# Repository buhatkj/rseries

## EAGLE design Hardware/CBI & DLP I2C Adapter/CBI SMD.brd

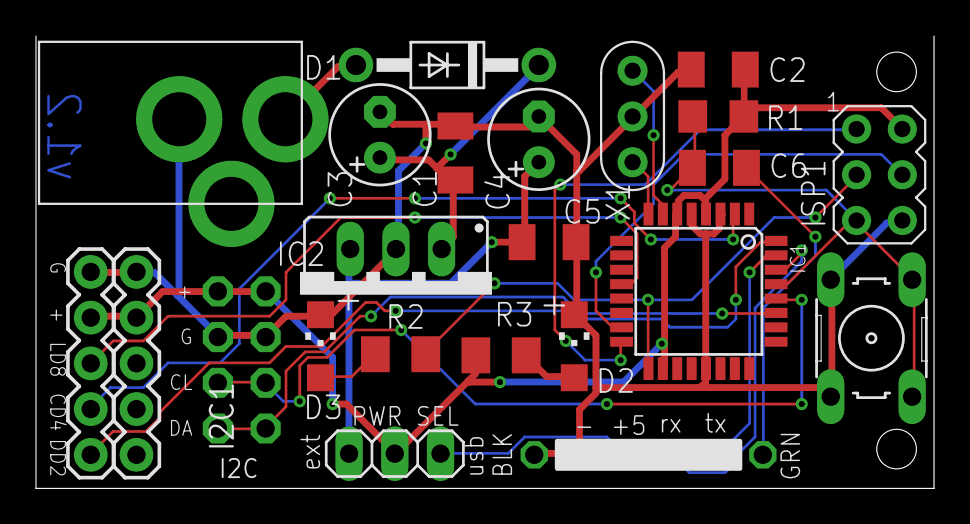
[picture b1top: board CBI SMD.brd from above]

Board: 2 copper layers, 49.9 x 25.1 mm, 25 parts (1 on the bottom side), 22 nets.

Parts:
C1, C2, C5, C6: 0.1uF; C1206K
C3: 10uF/25V; E2,5-6
C4: 100/6VuF; E2,5-6
D1: 1N4001; DO41-10
D2: CHIPLED_1206
D3: Green; CHIPLED_1206
I2C, I2C1: 1X04-CB
IC1: MEGA48/88/168-AU; TQFP32-08
IC2: 78XXS
ISP1: AVRISP-6; AVRISP
J1: 2.1MMJACK; PJ-102A
JP7: 1X06-CLEAN
PWR_SEL: 1X03
R1: 10K; R1206
R2, R3: 1.0 K; M1206
S1: RESET; B3F-10XX
TEECES, TEECES1: 1X05
U$2: RSERIES-OSHW-LOGOMEDIUM; RSERIES-OSHW-LOGO-MEDIUM
X1: 16.00MHz; CERM_OSC

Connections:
+5V: C2.1, I2C.4, I2C1.4, IC1.4, IC1.6, IC1.18, ISP1.2, PWR_SEL.2, R1.1, R2.1, TEECES.4, TEECES1.4
+9V: C1.1, C3.+, D1.C, IC2.IN
ANALOG4: I2C.1, I2C1.1, IC1.27
ANALOG5: I2C.2, I2C1.2, IC1.28
DIGITAL2: IC1.32, TEECES.1
DIGITAL4: IC1.2, TEECES.2
DIGITAL8: IC1.12, TEECES.3
GND: C1.2, C2.2, C3.-, C4.-, C5.2, D2.C, D3.C, I2C.3, I2C1.3, IC1.3, IC1.5, IC1.21, IC2.GND, ISP1.6, J1.RING, JP7.1, JP7.2, S1.1, S1.2, TEECES.5, TEECES1.5, X1.P$2
MISO: IC1.16, ISP1.1
MOSI: IC1.15, ISP1.4
unnamed: IC1.7, X1.P$1
unnamed: IC1.8, X1.P$3
unnamed: D2.A, R2.2
unnamed: D3.A, R3.2
unnamed: D1.A, J1.TIP
unnamed: C4.+, C5.1, IC2.OUT, PWR_SEL.1
RST: C6.2, IC1.29, ISP1.5, R1.2, S1.3, S1.4
RTS#: C6.1, JP7.6
RXD: IC1.30, JP7.4
SCK: IC1.17, ISP1.3, R3.1
TXD: IC1.31, JP7.5
USB_5V: JP7.3, PWR_SEL.3

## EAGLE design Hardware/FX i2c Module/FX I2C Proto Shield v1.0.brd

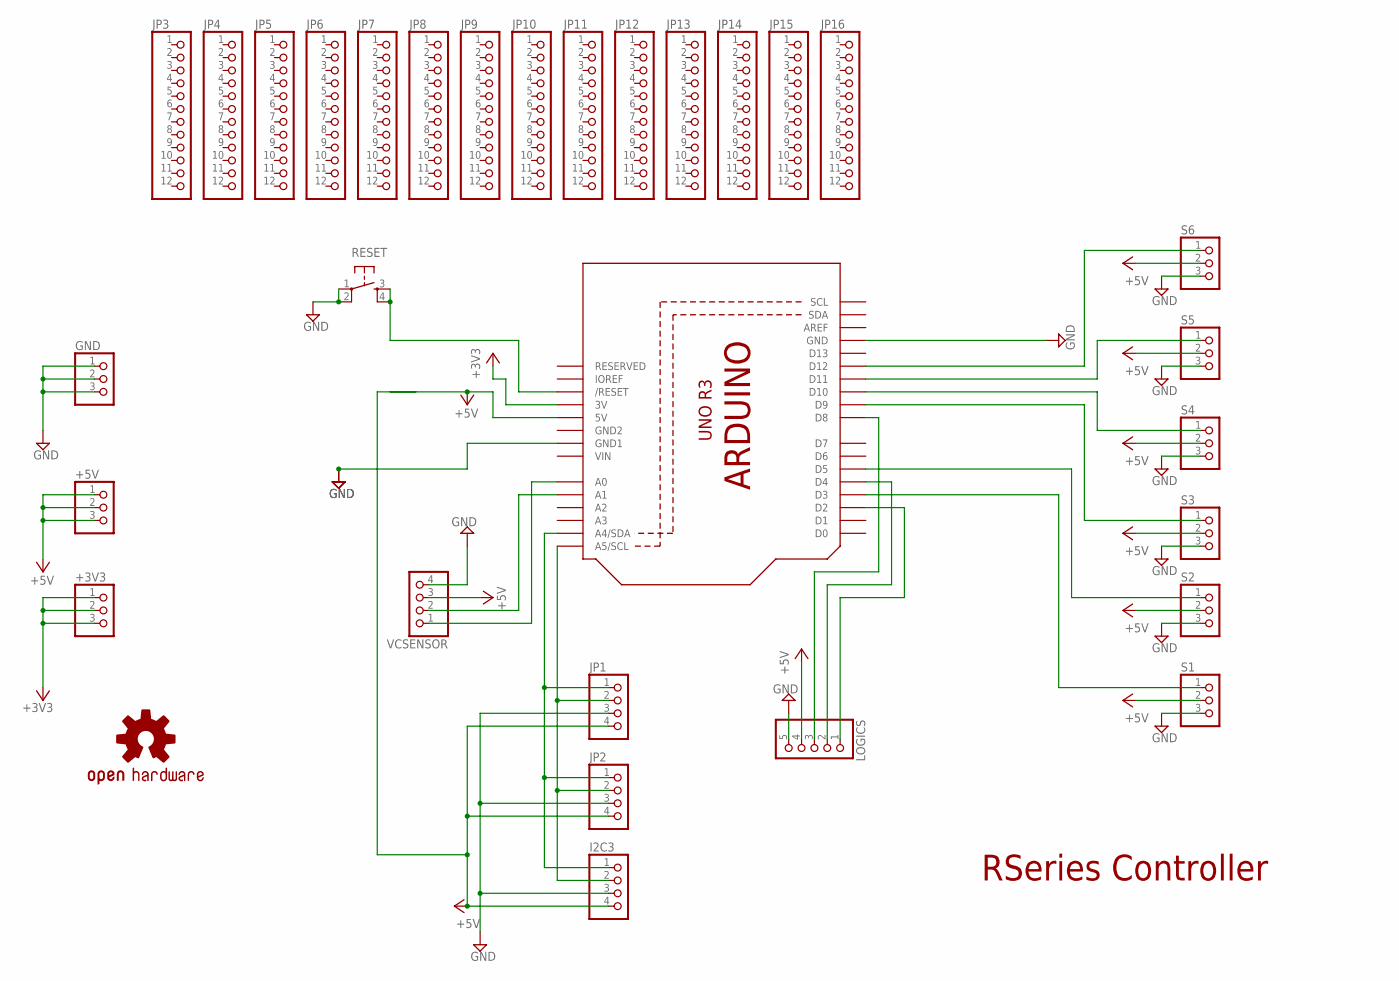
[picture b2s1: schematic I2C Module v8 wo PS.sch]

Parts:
+3V3, +5V: PINHD-1X3CB; 1X03-CLEANBIG
GND: PINHD-1X3CB; 1X03-CLEANBIG
I2C3: PINHD-1X4; 1X04
JP1, JP2: PINHD-1X4; 1X04
JP3, JP4, JP5, JP6, JP7, JP8, JP9, JP10, JP11, JP12, JP13, JP14, JP15, JP16: PINHD-1X12-CB; 1X12-CB
LOGICS: PINHD-1X5; 1X05
RESET: TAC_SWITCHPTH; TACTILE-PTH
S1, S2, S3, S4, S5, S6: PINHD-1X3; 1X03
U1: ARDUINOR3-DIMENSION; ARDUINOR3
U$1: OSHW-LOGOM; OSHW-LOGO-M
VCSENSOR: PINHD-1X4; 1X04

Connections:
+3V3: +3V3.1, +3V3.2, +3V3.3, U1.3V
+5V: +5V.1, +5V.2, +5V.3, I2C3.4, JP1.4, JP2.4, LOGICS.4, S1.2, S2.2, S3.2, S4.2, S5.2, S6.2, U1.5V, VCSENSOR.3
GND: GND.1, GND.2, GND.3, I2C3.3, JP1.3, JP2.3, LOGICS.5, RESET.1, RESET.2, S1.3, S2.3, S3.3, S4.3, S5.3, S6.3, U1.GND, U1.GND1, VCSENSOR.4
GND2: U1.GND2
unnamed 4: U1.A0, VCSENSOR.1; also elsewhere on the board
unnamed 5: LOGICS.3, U1.D8; also elsewhere on the board
unnamed 6: U1.A1, VCSENSOR.2; also elsewhere on the board
unnamed 7: S1.1, U1.D3; also elsewhere on the board
unnamed 8: S2.1, U1.D5; also elsewhere on the board
unnamed 9: S3.1, U1.D9; also elsewhere on the board
unnamed 10: S4.1, U1.D10; also elsewhere on the board
unnamed 11: S5.1, U1.D11; also elsewhere on the board
unnamed 12: S6.1, U1.D12; also elsewhere on the board
unnamed 13: LOGICS.2, U1.D4; also elsewhere on the board
unnamed 14: LOGICS.1, U1.D2; also elsewhere on the board
unnamed: RESET.3, RESET.4, U1.RESET (/RESET)
unnamed 17: U1.A2; also elsewhere on the board
unnamed 18: I2C3.2, JP1.2, JP2.2, U1.A5 (A5/SCL); also elsewhere on the board
unnamed 19: I2C3.1, JP1.1, JP2.1, U1.A4 (A4/SDA); also elsewhere on the board
unnamed 20: U1.A3; also elsewhere on the board
unnamed 21: U1.D0; also elsewhere on the board
unnamed 22: U1.D1; also elsewhere on the board
unnamed 23: U1.D6; also elsewhere on the board
unnamed 24: U1.D7; also elsewhere on the board
unnamed 25: U1.D13; also elsewhere on the board
VIN: U1.VIN

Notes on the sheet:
RSeries Controller

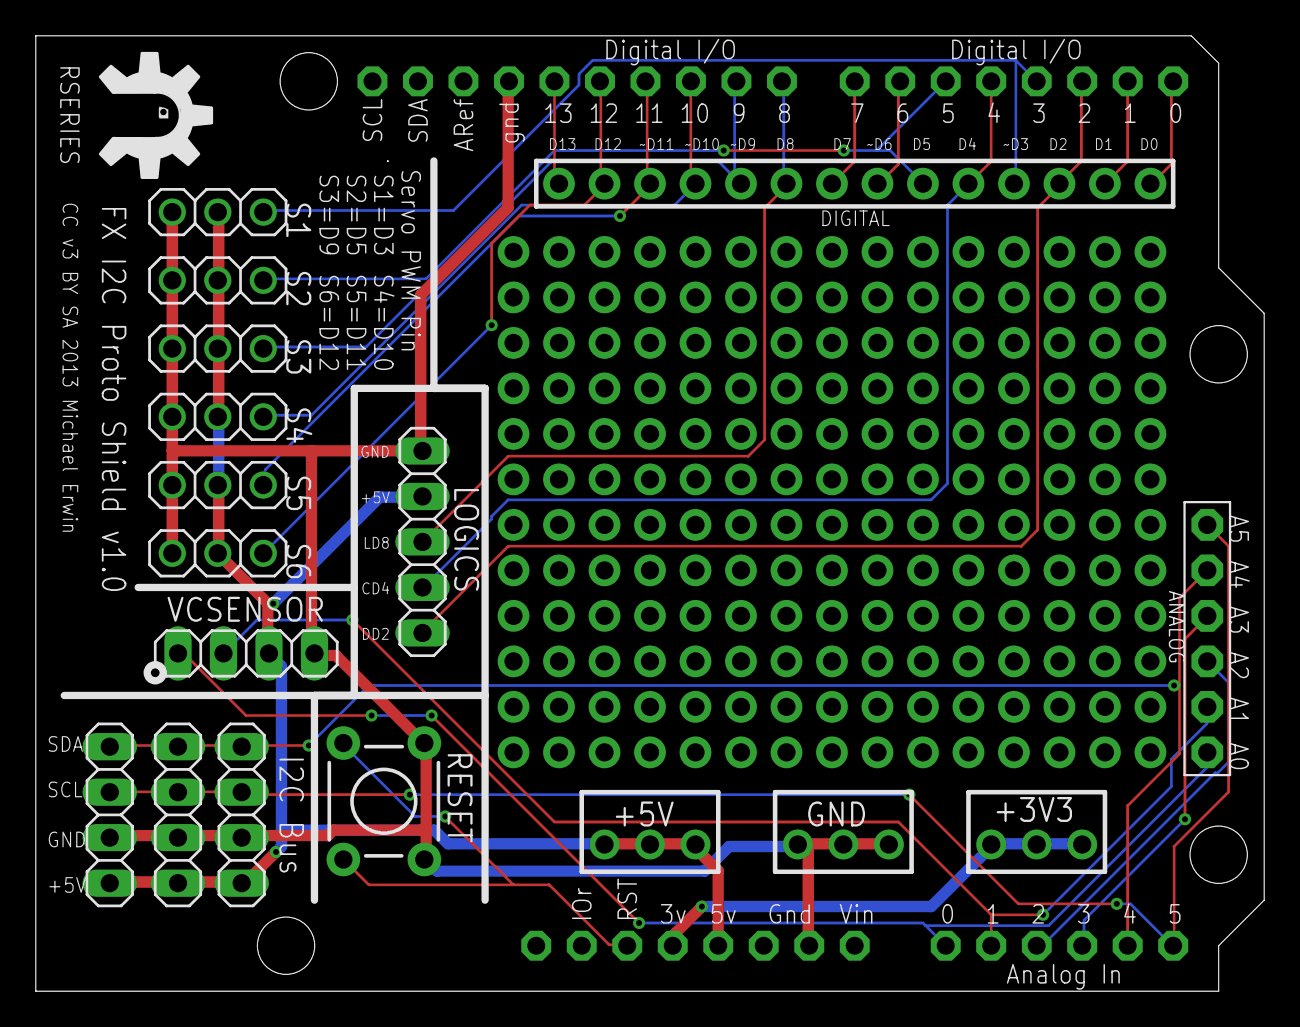
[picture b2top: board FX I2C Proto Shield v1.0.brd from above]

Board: 2 copper layers, 68.6 x 53.3 mm, 34 parts (0 on the bottom side), 24 nets.

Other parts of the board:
ANALOG: 1X06-BIG
DIGITAL: 1X14-CB
JP17: 1X12-CB

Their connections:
unnamed 4: ANALOG.1; also elsewhere on the board
unnamed 5: DIGITAL.9; also elsewhere on the board
unnamed 6: ANALOG.2; also elsewhere on the board
unnamed 7: DIGITAL.4; also elsewhere on the board
unnamed 8: DIGITAL.6; also elsewhere on the board
unnamed 9: DIGITAL.10; also elsewhere on the board
unnamed 10: DIGITAL.11; also elsewhere on the board
unnamed 11: DIGITAL.12; also elsewhere on the board
unnamed 12: DIGITAL.13; also elsewhere on the board
unnamed 13: DIGITAL.5; also elsewhere on the board
unnamed 14: DIGITAL.3; also elsewhere on the board
unnamed 17: ANALOG.3; also elsewhere on the board
unnamed 18: ANALOG.6; also elsewhere on the board
unnamed 19: ANALOG.5; also elsewhere on the board
unnamed 20: ANALOG.4; also elsewhere on the board
unnamed 21: DIGITAL.1; also elsewhere on the board
unnamed 22: DIGITAL.2; also elsewhere on the board
unnamed 23: DIGITAL.7; also elsewhere on the board
unnamed 24: DIGITAL.8; also elsewhere on the board
unnamed 25: DIGITAL.14; also elsewhere on the board

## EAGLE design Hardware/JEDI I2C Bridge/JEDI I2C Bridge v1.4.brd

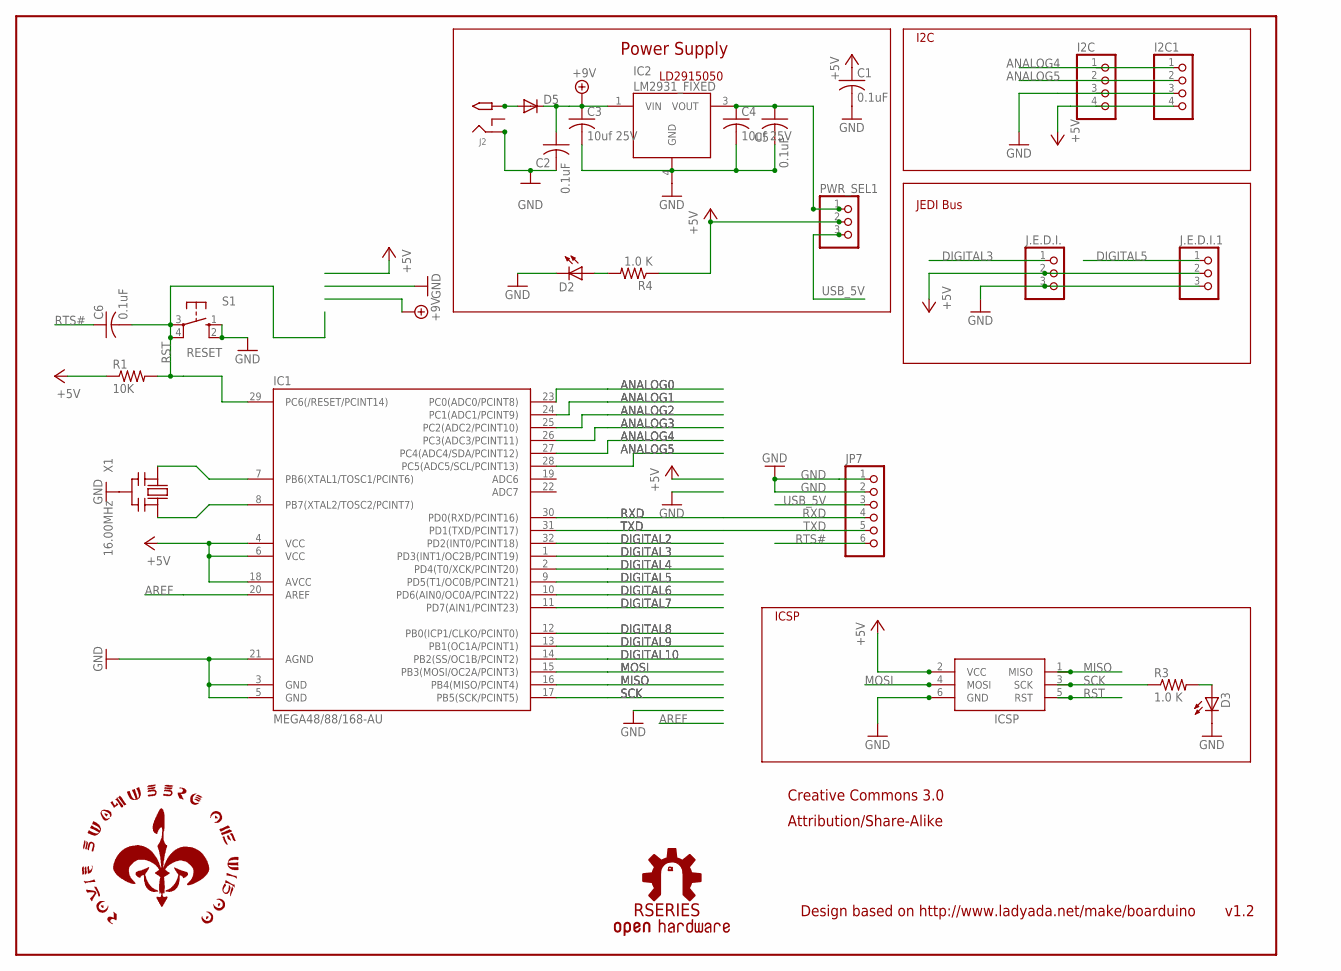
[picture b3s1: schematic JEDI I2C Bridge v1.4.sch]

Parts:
C1, C2, C5, C6: 0.1uF; C1206K
C3, C4: 10uf 25V; C1206K
D2: LEDCHIPLED_1206; CHIPLED_1206
D3: Green; CHIPLED_1206
D5: DIODE-SMB; SMB
I2C, I2C1: PINHD-1X4CB; 1X04-CB
IC1: MEGA48/88/168-AU; TQFP32-08
IC2: LM2931_FIXED; DPAK
ICSP: AVRISP-6; AVRISP
J2: 2.1MMJACK; PJ-102A
J.E.D.I., J.E.D.I.1: PINHD-1X3; 1X03
JP7: PINHD-1X6CLEAN; 1X06-CLEAN
PWR_SEL1: PINHD-1X3; 1X03
R1: 10K; R1206
R3, R4: 1.0 K; M1206
S1: RESET; B3F-10XX
U$2: RSERIES-OSHW-LOGOMEDIUM; RSERIES-OSHW-LOGO-MEDIUM
U$3: ROYAL-ENGINEERS-OF-NABOOSMALL; ROYAL-ENGINEERS-OF-NABOO-SMALL
X1: 16.00MHz; CERM_OSC

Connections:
+5V: C1.1, I2C.4, I2C1.4, IC1.4 (VCC), IC1.6 (VCC), IC1.18 (AVCC), ICSP.2 (VCC), J.E.D.I..2, J.E.D.I.1.2, PWR_SEL1.2, R1.1, R4.1
+9V: C2.1, C3.1, D5.C, IC2.1 (VIN)
ANALOG0: IC1.23 (PC0(ADC0/PCINT8))
ANALOG1: IC1.24 (PC1(ADC1/PCINT9))
ANALOG2: IC1.25 (PC2(ADC2/PCINT10))
ANALOG3: IC1.26 (PC3(ADC3/PCINT11))
ANALOG4: I2C.1, I2C1.1, IC1.27 (PC4(ADC4/SDA/PCINT12))
ANALOG5: I2C.2, I2C1.2, IC1.28 (PC5(ADC5/SCL/PCINT13))
AREF: IC1.20 (AREF)
DIGITAL2: IC1.32 (PD2(INT0/PCINT18))
DIGITAL3: IC1.1 (PD3(INT1/OC2B/PCINT19)), J.E.D.I..1
DIGITAL4: IC1.2 (PD4(T0/XCK/PCINT20))
DIGITAL5: IC1.9 (PD5(T1/OC0B/PCINT21)), J.E.D.I.1.1
DIGITAL6: IC1.10 (PD6(AIN0/OC0A/PCINT22))
DIGITAL7: IC1.11 (PD7(AIN1/PCINT23))
DIGITAL8: IC1.12 (PB0(ICP1/CLKO/PCINT0))
DIGITAL9: IC1.13 (PB1(OC1A/PCINT1))
DIGITAL10: IC1.14 (PB2(SS/OC1B/PCINT2))
GND: C1.2, C2.2, D2.C, D3.C, I2C.3, I2C1.3, IC1.3 (GND), IC1.5 (GND), IC1.21 (AGND), IC2.4 (GND), ICSP.6 (GND), J2.RING, J.E.D.I..3, J.E.D.I.1.3, JP7.1, JP7.2, S1.1 (S), S1.2 (S1), X1.P$2 (GND)
MISO: IC1.16 (PB4(MISO/PCINT4)), ICSP.1 (MISO)
MOSI: IC1.15 (PB3(MOSI/OC2A/PCINT3)), ICSP.4 (MOSI)
unnamed: IC1.7 (PB6(XTAL1/TOSC1/PCINT6)), X1.P$1 (IN)
unnamed: IC1.8 (PB7(XTAL2/TOSC2/PCINT7)), X1.P$3 (OUT)
unnamed: D3.A, R3.2
unnamed: D2.A, R4.2
unnamed: D5.A, J2.TIP
unnamed: C3.2, C4.2, C5.2
unnamed: C4.1, C5.1, IC2.3 (VOUT), PWR_SEL1.1
RST: C6.2, IC1.29 (PC6(/RESET/PCINT14)), ICSP.5 (RST), R1.2, S1.3, S1.4 (P1)
RTS#: C6.1, JP7.6
RXD: IC1.30 (PD0(RXD/PCINT16)), JP7.4
SCK: IC1.17 (PB5(SCK/PCINT5)), ICSP.3 (SCK), R3.1
TXD: IC1.31 (PD1(TXD/PCINT17)), JP7.5
USB_5V: JP7.3, PWR_SEL1.3

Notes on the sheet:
v1.2
Design based on http://www.ladyada.net/make/boarduino
Creative Commons 3.0
Attribution/Share-Alike
JEDI Bus
I2C
ICSP
Power Supply
LD2915050

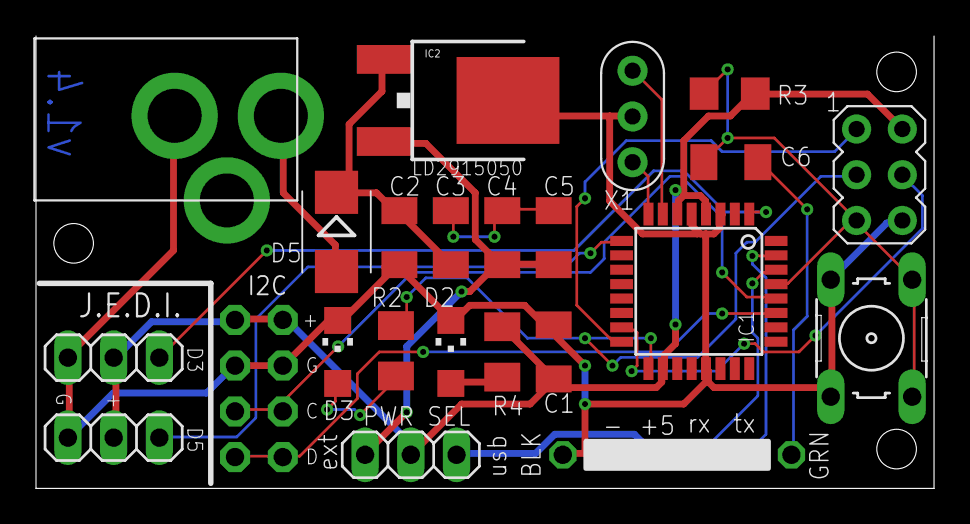
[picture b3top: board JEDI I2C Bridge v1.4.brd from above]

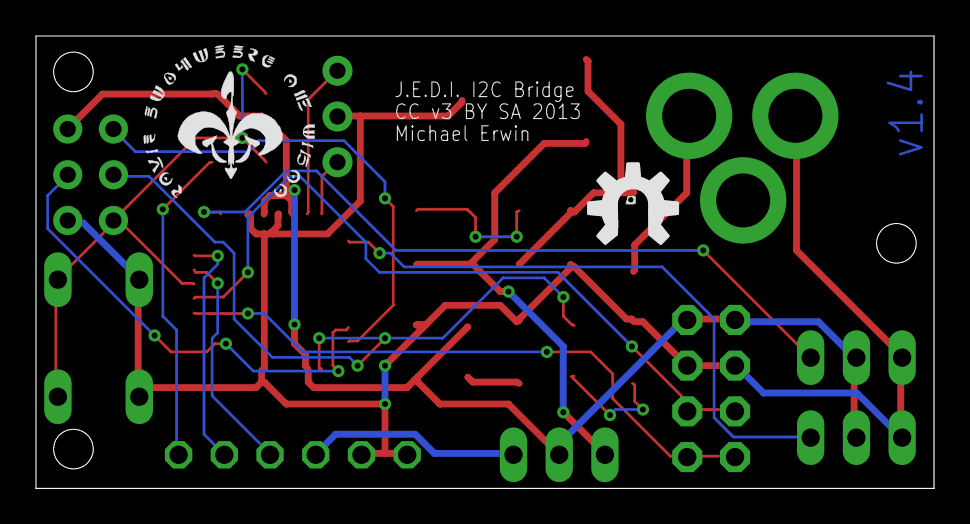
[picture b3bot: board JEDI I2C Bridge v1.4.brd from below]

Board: 2 copper layers, 49.9 x 25.1 mm, 26 parts (2 on the bottom side), 22 nets.

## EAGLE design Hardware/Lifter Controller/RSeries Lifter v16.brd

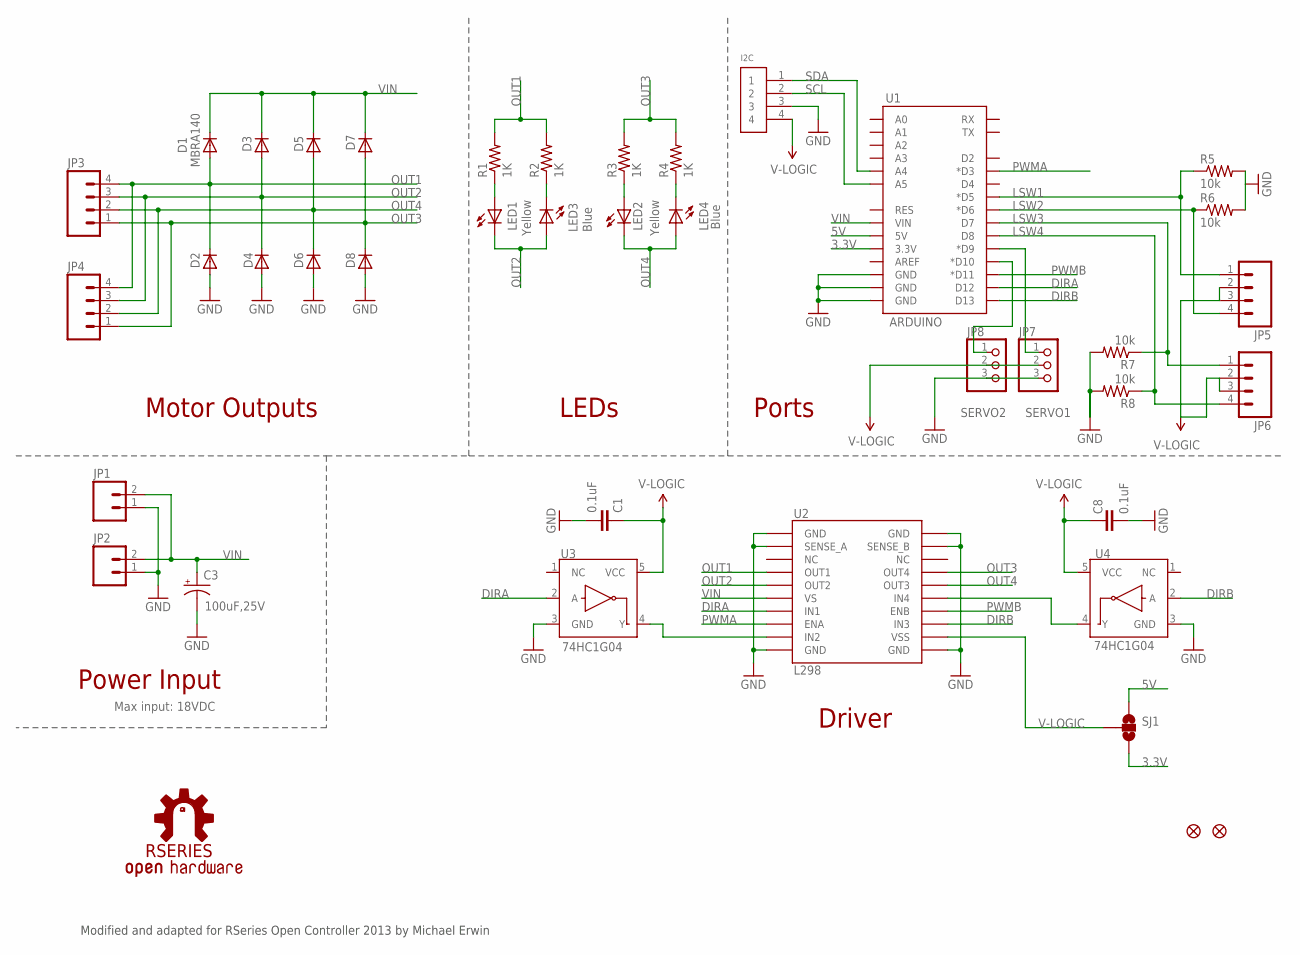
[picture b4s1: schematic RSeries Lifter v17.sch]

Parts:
C1, C8: 0.1uF; 0402-CAP
C3: 100uF,25V; NIPPON_F80
D1, D2, D3, D4, D5, D6, D7, D8: MBRA140; SMA-DIODE
I2C: 1X4-CLEANBIG; 1X04-CLEANBIG
JP1: M02PTH; 1X02
JP2: M023.5MM; SCREWTERMINAL-3.5MM-2
JP3, JP5, JP6: M04SCREW; SCREWTERMINAL-3.5MM-4
JP4: M04PTH; 1X04
JP7, JP8: PINHD-1X3CB; 1X03-CLEANBIG
LED1, LED2: Yellow; LED-1206
LED3, LED4: Blue; LED-1206
R1, R2, R3, R4: 1K; 0805
R5, R6, R7, R8: 10k; 0805
SJ1: SOLDERJUMPER_2WAYPASTE1&2; SJ_3_PASTE1&2
U1: ARDUINO; DUEMILANOVE_SHIELD_NOLABELS
U2: L298; POWERSO20
U3, U4: 74HC1G04; SOT23-5
U$3, U$4: FIDUCIAL1X2; FIDUCIAL-1X2
U$7: RSERIES-OSHW-LOGOMEDIUM; RSERIES-OSHW-LOGO-MEDIUM

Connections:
3.3V: SJ1.3, U1.3.3V
5V: I2C.4, JP5.2, JP5.3, JP6.2, JP6.3, JP7.2, JP8.2, SJ1.1, U1.5V
DIRA: U1.D12, U2.P$7 (IN1), U3.2 (A)
DIRB: U1.D13, U2.P$13 (IN3), U4.2 (A)
GND: C1.2, C3.-, C8.2, D2.A, D4.A, D6.A, D8.A, I2C.3, JP1.1, JP2.1, JP7.3, JP8.3, R5.2, R6.2, R7.2, R8.2, U1.GND@0 (GND), U1.GND@1 (GND), U1.GND@2 (GND), U2.P$1 (GND), U2.P$2 (SENSE_A), U2.P$10 (GND), U2.P$11 (GND), U2.P$19 (SENSE_B), U2.P$20 (GND), U3.3 (GND), U4.3 (GND)
unnamed: U2.P$9 (IN2), U3.4 (Y)
unnamed: U2.P$15 (IN4), U4.4 (Y)
unnamed: JP5.1, R5.1, U1.D5 (*D5)
unnamed: LED1.A, R1.1
unnamed: LED3.C, R2.1
unnamed: JP6.1, R7.1, U1.D7
unnamed: JP6.4, R8.1, U1.D8
unnamed: LED2.A, R3.1
unnamed: LED4.C, R4.1
unnamed: JP7.1, U1.D9 (*D9)
unnamed: JP8.1, U1.D10 (*D10)
unnamed: JP5.4, R6.1, U1.D6 (*D6)
unnamed: I2C.1, U1.A4
unnamed: I2C.2, U1.A5
OUT1: D1.A, D2.C, JP3.4, JP4.4, R1.2, R2.2, U2.P$4 (OUT1)
OUT2: D3.A, D4.C, JP3.3, JP4.3, LED1.C, LED3.A, U2.P$5 (OUT2)
OUT3: D7.A, D8.C, JP3.1, JP4.1, R3.2, R4.2, U2.P$17 (OUT4)
OUT4: D5.A, D6.C, JP3.2, JP4.2, LED2.C, LED4.A, U2.P$16 (OUT3)
PWMA: U1.D3 (*D3), U2.P$8 (ENA)
PWMB: U1.D11 (*D11), U2.P$14 (ENB)
V-LOGIC: C1.1, C8.1, SJ1.2, U2.P$12 (VSS), U3.5 (VCC), U4.5 (VCC)
VIN: C3.+, D1.C, D3.C, D5.C, D7.C, JP1.2, JP2.2, U1.VIN, U2.P$6 (VS)

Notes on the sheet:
Motor Outputs
LEDs
Ports
Driver
Power Input
Max input: 18VDC
Modified and adapted for RSeries Open Controller 2013 by Michael Erwin
SERVO1
SERVO2
SDA
SCL
LSW1
LSW2
LSW3
LSW4

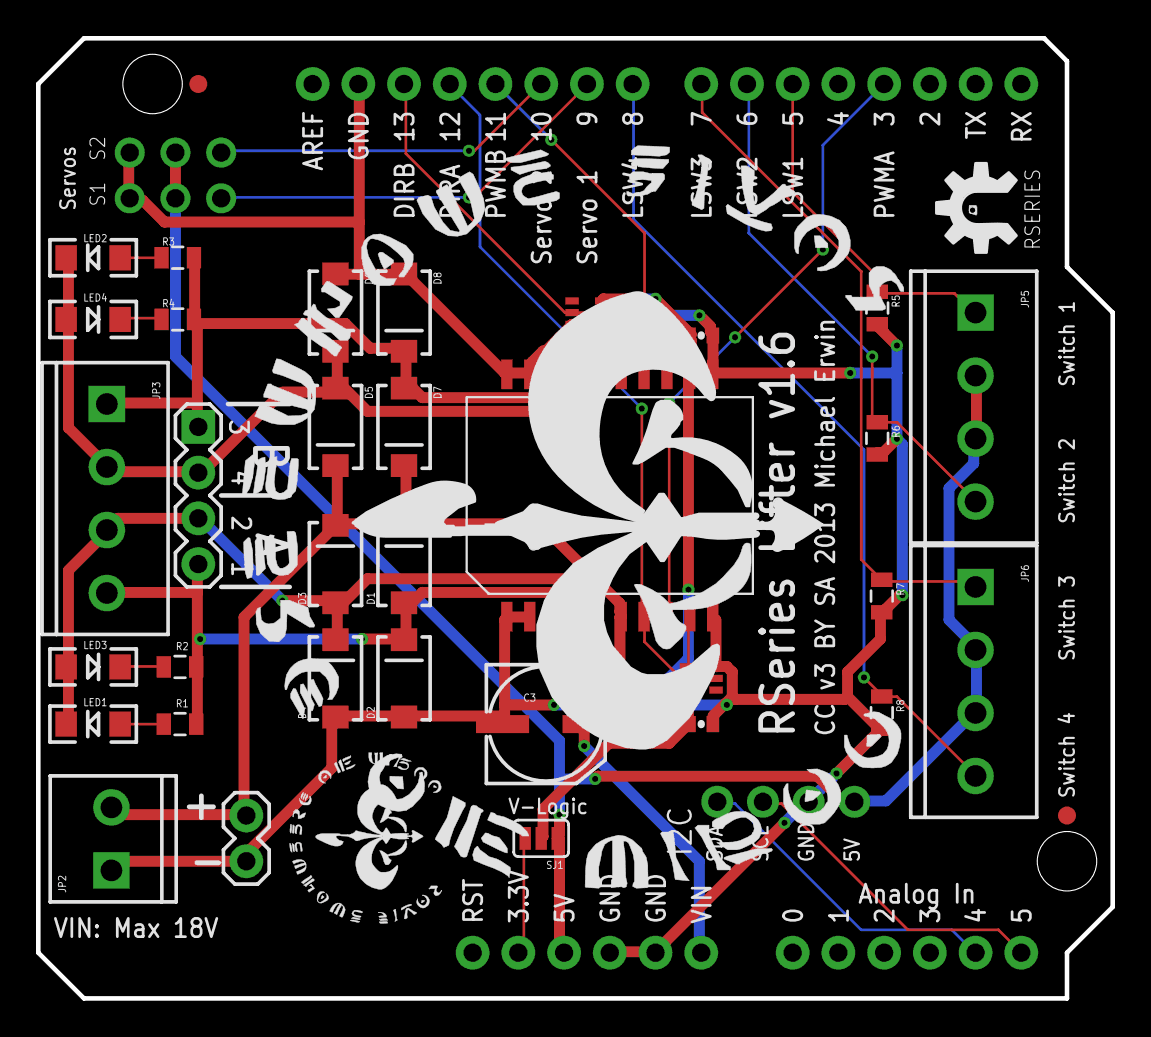
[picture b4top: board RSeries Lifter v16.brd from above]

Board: 2 copper layers, 59.7 x 53.3 mm, 42 parts (1 on the bottom side), 27 nets.

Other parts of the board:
U$6: ROYAL-ENGINEERS-OF-NABOO-SMALL
U$10: ROYAL-ENGINEERS-OF-NABOO-BOTTOM-LARGE

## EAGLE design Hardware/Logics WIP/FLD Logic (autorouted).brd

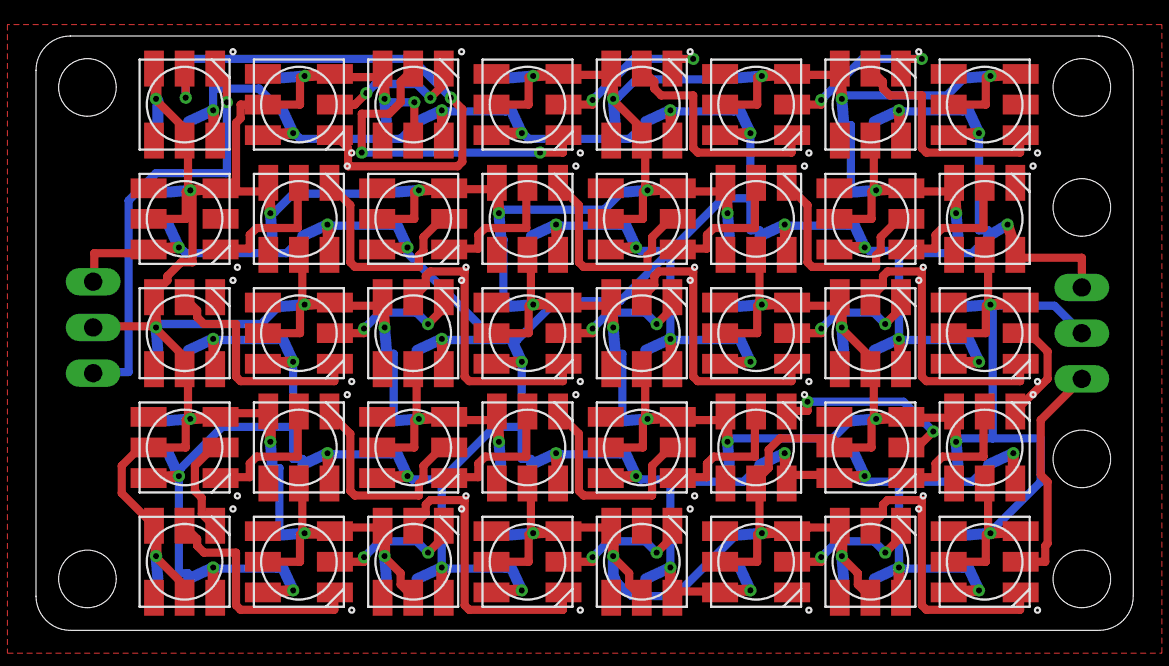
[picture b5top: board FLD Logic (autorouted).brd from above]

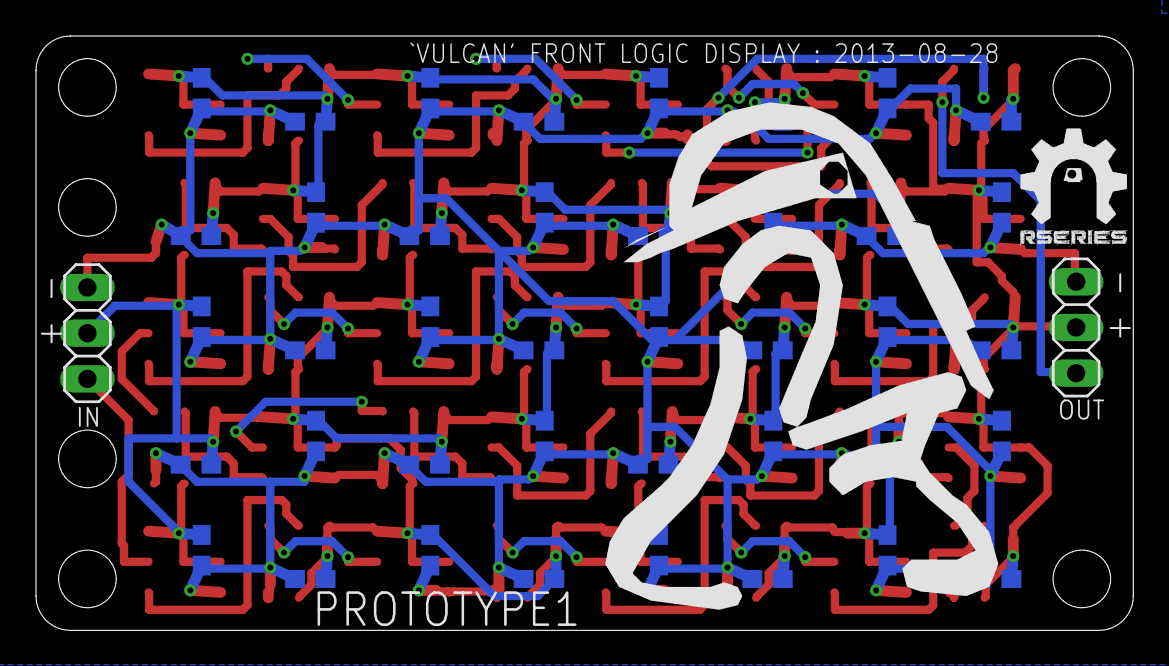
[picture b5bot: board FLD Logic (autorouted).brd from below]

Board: 2 copper layers, 61.0 x 33.0 mm, 83 parts (43 on the bottom side), 40 nets.

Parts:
C1, C2, C3, C4, C5, C6, C7, C8, C9, C10, C11, C12, C13, C14, C15, C16, C17, C18, C19, C20, C21, C22, C23, C24, C25, C26, C27, C28, C29, C30, C31, C32, C33, C34, C35, C36, C37, C38, C39, C40: 0.1uF; C0603
IN: 1X03
LED1, LED2, LED3, LED4, LED5, LED6, LED7, LED8, LED9, LED10, LED11, LED12, LED13, LED14, LED15, LED16, LED17, LED18, LED19, LED20, LED21, LED22, LED23, LED24, LED25, LED26, LED27, LED28, LED29, LED30, LED31, LED32, LED33, LED34, LED35, LED36, LED37, LED38, LED39, LED40: WS2812
OUT: 1X03
U$1: RSERIES-OSHW-LOGO-SMALL

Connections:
+5V: C1.1, C2.1, C3.1, C4.1, C5.1, C6.1, C7.1, C8.1, C9.1, C10.1, C11.1, C12.1, C13.1, C14.1, C15.1, C16.1, C17.1, C18.1, C19.1, C20.1, C21.1, C22.1, C23.1, C24.1, C25.1, C26.1, C27.1, C28.1, C29.1, C30.1, C31.1, C32.1, C33.1, C34.1, C35.1, C36.1, C37.1, C38.1, C39.1, C40.1, IN.2, LED1.LEDVDD, LED1.VDD, LED2.LEDVDD, LED2.VDD, LED3.LEDVDD, LED3.VDD, LED4.LEDVDD, LED4.VDD, LED5.LEDVDD, LED5.VDD, LED6.LEDVDD, LED6.VDD, LED7.LEDVDD, LED7.VDD, LED8.LEDVDD, LED8.VDD, LED9.LEDVDD, LED9.VDD, LED10.LEDVDD, LED10.VDD, LED11.LEDVDD, LED11.VDD, LED12.LEDVDD, LED12.VDD, LED13.LEDVDD, LED13.VDD, LED14.LEDVDD, LED14.VDD, LED15.LEDVDD, LED15.VDD, LED16.LEDVDD, LED16.VDD, LED17.LEDVDD, LED17.VDD, LED18.LEDVDD, LED18.VDD, LED19.LEDVDD, LED19.VDD, LED20.LEDVDD, LED20.VDD, LED21.LEDVDD, LED21.VDD, LED22.LEDVDD, LED22.VDD, LED23.LEDVDD, LED23.VDD, LED24.LEDVDD, LED24.VDD, LED25.LEDVDD, LED25.VDD, LED26.LEDVDD, LED26.VDD, LED27.LEDVDD, LED27.VDD, LED28.LEDVDD, LED28.VDD, LED29.LEDVDD, LED29.VDD, LED30.LEDVDD, LED30.VDD, LED31.LEDVDD, LED31.VDD, LED32.LEDVDD, LED32.VDD, LED33.LEDVDD, LED33.VDD, LED34.LEDVDD, LED34.VDD, LED35.LEDVDD, LED35.VDD, LED36.LEDVDD, LED36.VDD, LED37.LEDVDD, LED37.VDD, LED38.LEDVDD, LED38.VDD, LED39.LEDVDD, LED39.VDD, LED40.LEDVDD, LED40.VDD, OUT.2
DIN: IN.3, LED1.DI
DOUT: LED40.DO, OUT.3
GND: C1.2, C2.2, C3.2, C4.2, C5.2, C6.2, C7.2, C8.2, C9.2, C10.2, C11.2, C12.2, C13.2, C14.2, C15.2, C16.2, C17.2, C18.2, C19.2, C20.2, C21.2, C22.2, C23.2, C24.2, C25.2, C26.2, C27.2, C28.2, C29.2, C30.2, C31.2, C32.2, C33.2, C34.2, C35.2, C36.2, C37.2, C38.2, C39.2, C40.2, IN.1, LED1.VSS, LED2.VSS, LED3.VSS, LED4.VSS, LED5.VSS, LED6.VSS, LED7.VSS, LED8.VSS, LED9.VSS, LED10.VSS, LED11.VSS, LED12.VSS, LED13.VSS, LED14.VSS, LED15.VSS, LED16.VSS, LED17.VSS, LED18.VSS, LED19.VSS, LED20.VSS, LED21.VSS, LED22.VSS, LED23.VSS, LED24.VSS, LED25.VSS, LED26.VSS, LED27.VSS, LED28.VSS, LED29.VSS, LED30.VSS, LED31.VSS, LED32.VSS, LED33.VSS, LED34.VSS, LED35.VSS, LED36.VSS, LED37.VSS, LED38.VSS, LED39.VSS, LED40.VSS, OUT.1
unnamed: LED4.DO, LED5.DI
unnamed: LED5.DO, LED6.DI
unnamed: LED7.DO, LED8.DI
unnamed: LED6.DO, LED7.DI
unnamed: LED17.DO, LED18.DI
unnamed: LED9.DO, LED10.DI
unnamed: LED10.DO, LED11.DI
unnamed: LED12.DO, LED13.DI
unnamed: LED13.DO, LED14.DI
unnamed: LED1.DO, LED2.DI
unnamed: LED2.DO, LED3.DI
unnamed: LED11.DO, LED12.DI
unnamed: LED15.DO, LED16.DI
unnamed: LED14.DO, LED15.DI
unnamed: LED16.DO, LED17.DI
unnamed: LED18.DO, LED19.DI
unnamed: LED20.DO, LED21.DI
unnamed: LED21.DO, LED22.DI
unnamed: LED19.DO, LED20.DI
unnamed: LED23.DO, LED24.DI
unnamed: LED22.DO, LED23.DI
unnamed: LED25.DO, LED26.DI
unnamed: LED26.DO, LED27.DI
unnamed: LED28.DO, LED29.DI
unnamed: LED29.DO, LED30.DI
unnamed: LED27.DO, LED28.DI
unnamed: LED31.DO, LED32.DI
unnamed: LED30.DO, LED31.DI
unnamed: LED33.DO, LED34.DI
unnamed: LED34.DO, LED35.DI
unnamed: LED36.DO, LED37.DI
unnamed: LED37.DO, LED38.DI
unnamed: LED35.DO, LED36.DI
unnamed: LED39.DO, LED40.DI
unnamed: LED38.DO, LED39.DI
unnamed: LED8.DO, LED9.DI

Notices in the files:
parts and their libraries:
SparkFun-Connectors: Licensing: CC v3.0 Share-Alike You are welcome to use this library for commercial purposes.
